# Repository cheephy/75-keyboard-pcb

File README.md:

# 75% keyboard
 A test project following master zen's "How to make a keyboard from scratch" to make a gmmk pro 75% layout style keybord using KiCad and FreeCad.

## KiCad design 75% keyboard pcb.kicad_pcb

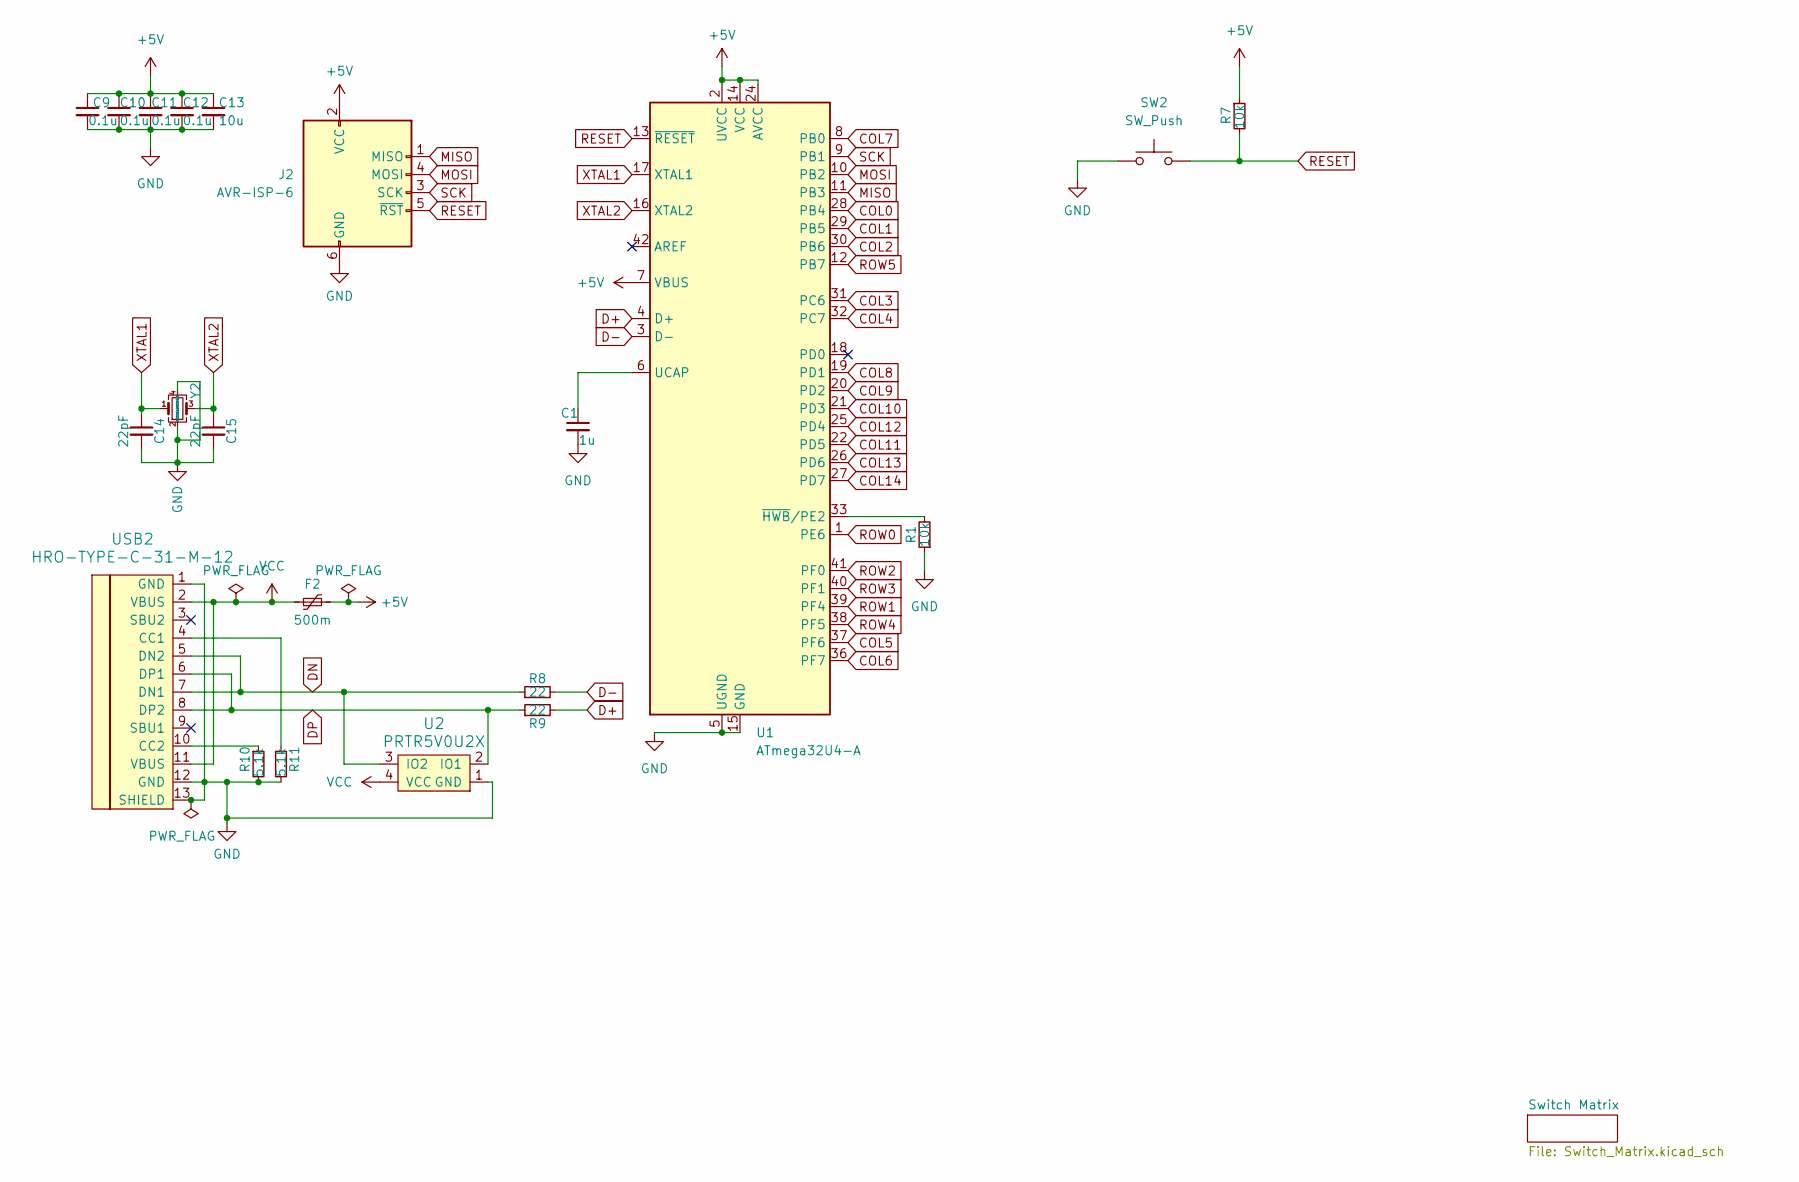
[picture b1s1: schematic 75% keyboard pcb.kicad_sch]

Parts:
C1: 1u; C_0805_2012Metric_Pad1.18x1.45mm_HandSolder
C9, C10, C11, C12: 0.1u; C_0805_2012Metric_Pad1.18x1.45mm_HandSolder
C13: 10u; C_0805_2012Metric_Pad1.18x1.45mm_HandSolder
C14, C15: 22pF; C_0805_2012Metric_Pad1.18x1.45mm_HandSolder
F2: 500m; Fuse_1206_3216Metric_Pad1.42x1.75mm_HandSolder
J2: AVR-ISP-6; Reset_Pretty-Mask
R1, R7: 10k; R_0805_2012Metric_Pad1.20x1.40mm_HandSolder
R8, R9: 22; R_0805_2012Metric_Pad1.20x1.40mm_HandSolder
R10, R11: 5.1k; R_0805_2012Metric_Pad1.20x1.40mm_HandSolder
SW2: SW_Push; SW_SPST_SKQG_WithStem
U1: ATmega32U4-A; TQFP-44_10x10mm_P0.8mm
U2: PRTR5V0U2X; SOT143B
USB2: HRO-TYPE-C-31-M-12; HRO-TYPE-C-31-M-12-HandSoldering
Y2: X322516MOB4SI; Crystal_SMD_3225-4Pin_3.2x2.5mm_HandSoldering

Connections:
+5V: C9.1, C10.1, C11.1, C12.1, C13.1, F2.2, J2.2 (VCC), R7.1, U1.2 (UVCC), U1.7 (VBUS), U1.14 (VCC), U1.24 (AVCC), U1.34 (VCC), U1.44 (AVCC)
COL0: U1.28 (PB4); also elsewhere on the board
COL1: U1.29 (PB5); also elsewhere on the board
COL2: U1.30 (PB6); also elsewhere on the board
COL3: U1.31 (PC6); also elsewhere on the board
COL4: U1.32 (PC7); also elsewhere on the board
COL5: U1.37 (PF6); also elsewhere on the board
COL6: U1.36 (PF7); also elsewhere on the board
COL7: U1.8 (PB0); also elsewhere on the board
COL8: U1.19 (PD1); also elsewhere on the board
COL9: U1.20 (PD2); also elsewhere on the board
COL10: U1.21 (PD3); also elsewhere on the board
COL11: U1.22 (PD5); also elsewhere on the board
COL12: U1.25 (PD4); also elsewhere on the board
COL13: U1.26 (PD6); also elsewhere on the board
COL14: U1.27 (PD7); also elsewhere on the board
D+: R9.2, U1.4 (D+)
D-: R8.2, U1.3 (D-)
DN: R8.1, U2.3 (IO2), USB2.5 (DN2), USB2.7 (DN1)
DP: R9.1, U2.2 (IO1), USB2.6 (DP1), USB2.8 (DP2)
GND: C1.2, C9.2, C10.2, C11.2, C12.2, C13.2, C14.2, C15.2, J2.6 (GND), R1.1, R10.2, R11.2, SW2.1, U1.5 (UGND), U1.15 (GND), U1.23 (GND), U1.35 (GND), U1.43 (GND), U2.1 (GND), USB2.1 (GND), USB2.12 (GND), USB2.13 (SHIELD), Y2.2, Y2.4
MISO: J2.1 (MISO), U1.11 (PB3)
MOSI: J2.4 (MOSI), U1.10 (PB2)
unnamed: C1.1, U1.6 (UCAP)
unnamed: R1.2, U1.33 (~HWB/PE2)
unnamed: R11.1, USB2.4 (CC1)
unnamed: R10.1, USB2.10 (CC2)
RESET: J2.5 (~RST), R7.2, SW2.2, U1.13 (~RESET)
ROW0: U1.1 (PE6); also elsewhere on the board
ROW2: U1.41 (PF0); also elsewhere on the board
ROW3: U1.40 (PF1); also elsewhere on the board
ROW5: U1.12 (PB7); also elsewhere on the board
SCK: J2.3 (SCK), U1.9 (PB1)
VCC: F2.1, U2.4 (VCC), USB2.2 (VBUS), USB2.11 (VBUS)
XTAL1: C14.1, U1.17 (XTAL1), Y2.1
XTAL2: C15.1, U1.16 (XTAL2), Y2.3

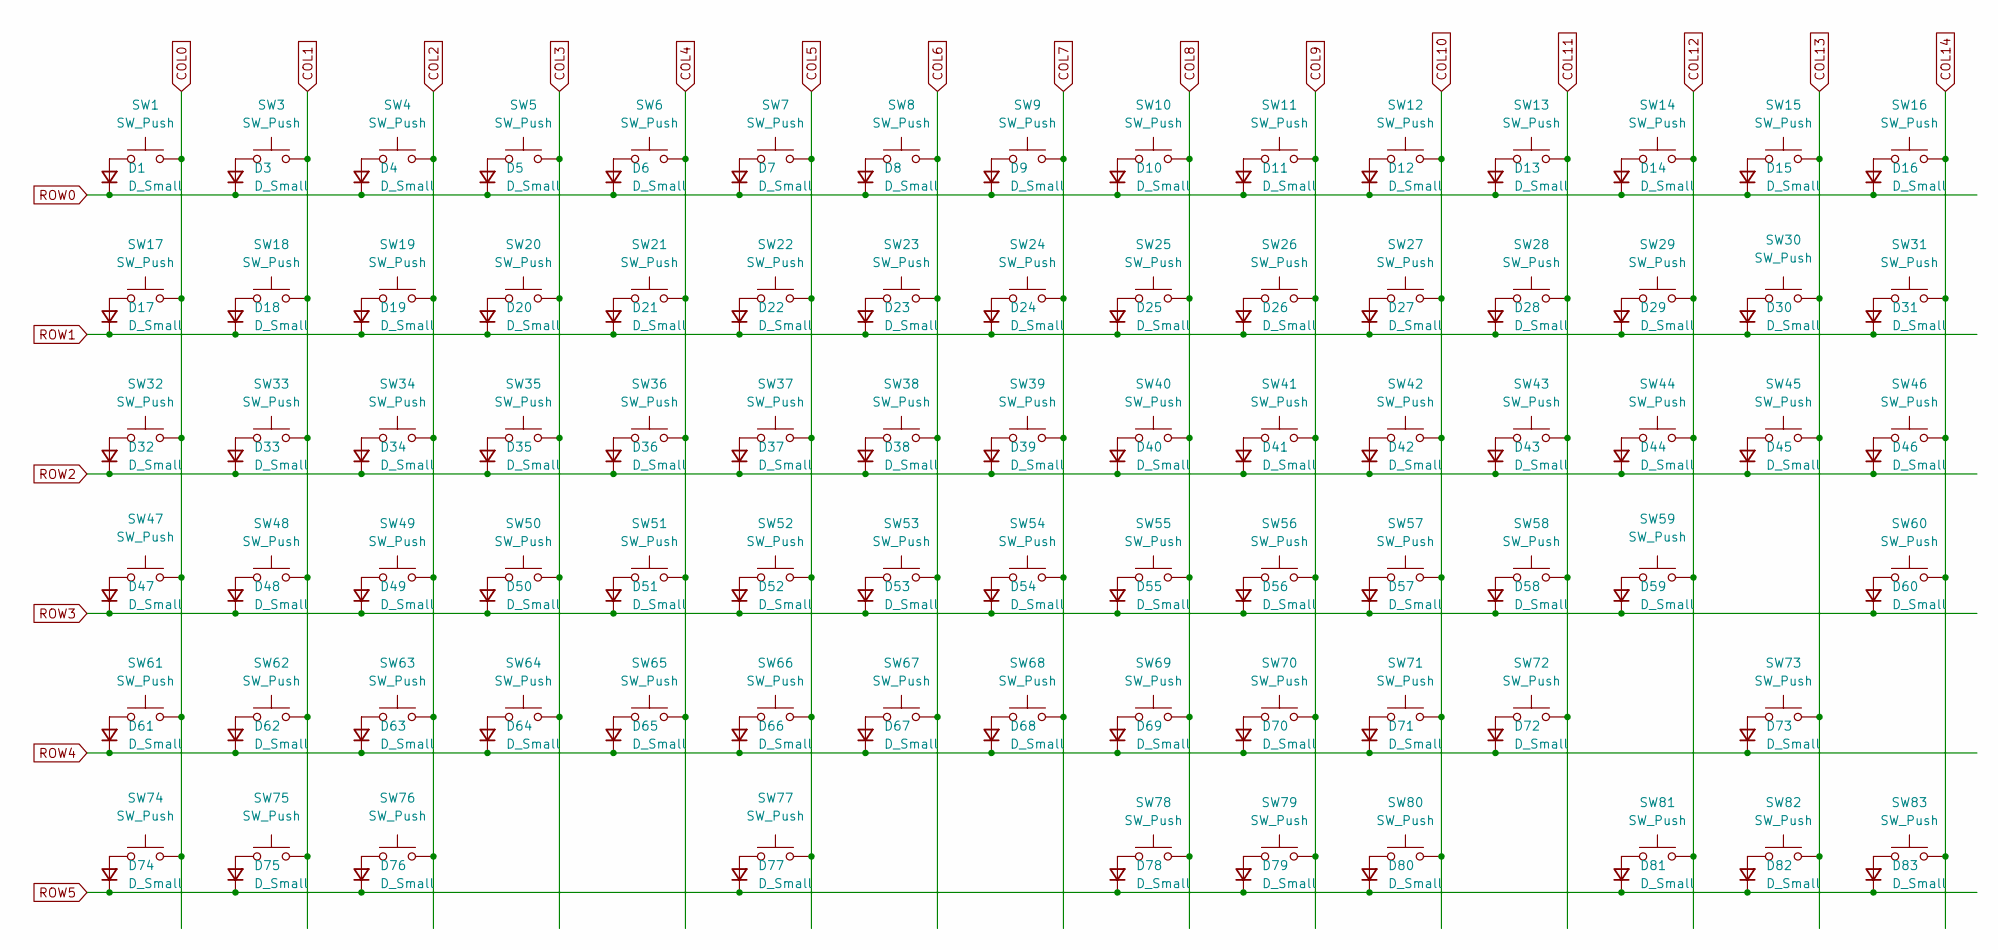
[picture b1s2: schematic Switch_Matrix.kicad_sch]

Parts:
D1, D3, D4, D5, D6, D7, D8, D9, D10, D11, D12, D13, D14, D15, D16, D17, D18, D19, D20, D21, D22, D23, D24, D25, D26, D27, D28, D29, D30, D31, D32, D33, D34, D35, D36, D37, D38, D39, D40, D41, D42, D43, D44, D45, D46, D47, D48, D49, D50, D51, D52, D53, D54, D55, D56, D57, D58, D59, D60, D61, D62, D63, D64, D65, D66, D67, D68, D69, D70, D71, D72, D73, D74, D75, D76, D77, D78, D79, D80, D81, D82, D83: D_Small; D_SOD-123
SW1, SW3, SW4, SW5, SW6, SW7, SW8, SW9, SW10, SW11, SW12, SW13, SW14, SW15, SW16, SW17, SW18, SW19, SW20, SW21, SW22, SW23, SW24, SW25, SW26, SW27, SW28, SW29, SW31, SW33, SW34, SW35, SW36, SW37, SW38, SW39, SW40, SW41, SW42, SW43, SW44, SW46, SW48, SW49, SW50, SW51, SW52, SW53, SW54, SW55, SW56, SW57, SW58, SW60, SW62, SW63, SW64, SW65, SW66, SW67, SW68, SW69, SW70, SW71, SW73, SW78, SW79, SW80, SW81, SW82, SW83: SW_Push; SW_Hotswap_Kailh_MX_Plated_1.00u
SW30: SW_Push; SW_Hotswap_Kailh_MX_Plated_2.00u
SW32, SW45: SW_Push; SW_Hotswap_Kailh_MX_Plated_1.50u
SW47, SW72: SW_Push; SW_Hotswap_Kailh_MX_Plated_1.75u
SW59, SW61: SW_Push; SW_Hotswap_Kailh_MX_Plated_2.25u
SW74, SW75, SW76: SW_Push; SW_Hotswap_Kailh_MX_Plated_1.25u
SW77: SW_Push; SW_Hotswap_Kailh_MX_Plated_6.25u

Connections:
COL0: SW1.2, SW17.2, SW32.2, SW47.2, SW61.2, SW74.2; also elsewhere on the board
COL1: SW3.2, SW18.2, SW33.2, SW48.2, SW62.2, SW75.2; also elsewhere on the board
COL2: SW4.2, SW19.2, SW34.2, SW49.2, SW63.2, SW76.2; also elsewhere on the board
COL3: SW5.2, SW20.2, SW35.2, SW50.2, SW64.2; also elsewhere on the board
COL4: SW6.2, SW21.2, SW36.2, SW51.2, SW65.2; also elsewhere on the board
COL5: SW7.2, SW22.2, SW37.2, SW52.2, SW66.2, SW77.2; also elsewhere on the board
COL6: SW8.2, SW23.2, SW38.2, SW53.2, SW67.2; also elsewhere on the board
COL7: SW9.2, SW24.2, SW39.2, SW54.2, SW68.2; also elsewhere on the board
COL8: SW10.2, SW25.2, SW40.2, SW55.2, SW69.2, SW78.2; also elsewhere on the board
COL9: SW11.2, SW26.2, SW41.2, SW56.2, SW70.2, SW79.2; also elsewhere on the board
COL10: SW12.2, SW27.2, SW42.2, SW57.2, SW71.2, SW80.2; also elsewhere on the board
COL11: SW13.2, SW28.2, SW43.2, SW58.2, SW72.2; also elsewhere on the board
COL12: SW14.2, SW29.2, SW44.2, SW59.2, SW81.2; also elsewhere on the board
COL13: SW15.2, SW30.2, SW45.2, SW73.2, SW82.2; also elsewhere on the board
COL14: SW16.2, SW31.2, SW46.2, SW60.2, SW83.2; also elsewhere on the board
unnamed: D1.2 (A), SW1.1
unnamed: D3.2 (A), SW3.1
unnamed: D4.2 (A), SW4.1
unnamed: D5.2 (A), SW5.1
unnamed: D6.2 (A), SW6.1
unnamed: D7.2 (A), SW7.1
unnamed: D8.2 (A), SW8.1
unnamed: D9.2 (A), SW9.1
unnamed: D10.2 (A), SW10.1
unnamed: D11.2 (A), SW11.1
unnamed: D12.2 (A), SW12.1
unnamed: D13.2 (A), SW13.1
unnamed: D14.2 (A), SW14.1
unnamed: D15.2 (A), SW15.1
unnamed: D16.2 (A), SW16.1
unnamed: D17.2 (A), SW17.1
unnamed: D18.2 (A), SW18.1
unnamed: D19.2 (A), SW19.1
unnamed: D20.2 (A), SW20.1
unnamed: D21.2 (A), SW21.1
unnamed: D22.2 (A), SW22.1
unnamed: D23.2 (A), SW23.1
unnamed: D24.2 (A), SW24.1
unnamed: D25.2 (A), SW25.1
unnamed: D26.2 (A), SW26.1
unnamed: D27.2 (A), SW27.1
unnamed: D28.2 (A), SW28.1
unnamed: D29.2 (A), SW29.1
unnamed: D30.2 (A), SW30.1
unnamed: D31.2 (A), SW31.1
unnamed: D32.2 (A), SW32.1
unnamed: D33.2 (A), SW33.1
unnamed: D34.2 (A), SW34.1
unnamed: D35.2 (A), SW35.1
unnamed: D36.2 (A), SW36.1
unnamed: D37.2 (A), SW37.1
unnamed: D38.2 (A), SW38.1
unnamed: D39.2 (A), SW39.1
unnamed: D40.2 (A), SW40.1
unnamed: D41.2 (A), SW41.1
unnamed: D42.2 (A), SW42.1
unnamed: D43.2 (A), SW43.1
unnamed: D44.2 (A), SW44.1
unnamed: D45.2 (A), SW45.1
unnamed: D46.2 (A), SW46.1
unnamed: D47.2 (A), SW47.1
unnamed: D48.2 (A), SW48.1
unnamed: D49.2 (A), SW49.1
unnamed: D50.2 (A), SW50.1
unnamed: D51.2 (A), SW51.1
unnamed: D52.2 (A), SW52.1
unnamed: D53.2 (A), SW53.1
unnamed: D54.2 (A), SW54.1
unnamed: D55.2 (A), SW55.1
unnamed: D56.2 (A), SW56.1
unnamed: D57.2 (A), SW57.1
unnamed: D58.2 (A), SW58.1
unnamed: D59.2 (A), SW59.1
unnamed: D60.2 (A), SW60.1
unnamed: D61.2 (A), SW61.1
unnamed: D62.2 (A), SW62.1
unnamed: D63.2 (A), SW63.1
unnamed: D64.2 (A), SW64.1
unnamed: D65.2 (A), SW65.1
unnamed: D66.2 (A), SW66.1
unnamed: D67.2 (A), SW67.1
unnamed: D68.2 (A), SW68.1
unnamed: D69.2 (A), SW69.1
unnamed: D70.2 (A), SW70.1
unnamed: D71.2 (A), SW71.1
unnamed: D72.2 (A), SW72.1
unnamed: D73.2 (A), SW73.1
unnamed: D74.2 (A), SW74.1
unnamed: D75.2 (A), SW75.1
unnamed: D76.2 (A), SW76.1
unnamed: D77.2 (A), SW77.1
unnamed: D78.2 (A), SW78.1
unnamed: D79.2 (A), SW79.1
unnamed: D80.2 (A), SW80.1
unnamed: D81.2 (A), SW81.1
unnamed: D82.2 (A), SW82.1
unnamed: D83.2 (A), SW83.1
ROW0: D1.1 (K), D3.1 (K), D4.1 (K), D5.1 (K), D6.1 (K), D7.1 (K), D8.1 (K), D9.1 (K), D10.1 (K), D11.1 (K), D12.1 (K), D13.1 (K), D14.1 (K), D15.1 (K), D16.1 (K); also elsewhere on the board
ROW2: D32.1 (K), D33.1 (K), D34.1 (K), D35.1 (K), D36.1 (K), D37.1 (K), D38.1 (K), D39.1 (K), D40.1 (K), D41.1 (K), D42.1 (K), D43.1 (K), D44.1 (K), D45.1 (K), D46.1 (K); also elsewhere on the board
ROW3: D47.1 (K), D48.1 (K), D49.1 (K), D50.1 (K), D51.1 (K), D52.1 (K), D53.1 (K), D54.1 (K), D55.1 (K), D56.1 (K), D57.1 (K), D58.1 (K), D59.1 (K), D60.1 (K); also elsewhere on the board
ROW5: D74.1 (K), D75.1 (K), D76.1 (K), D77.1 (K), D78.1 (K), D79.1 (K), D80.1 (K), D81.1 (K), D82.1 (K), D83.1 (K); also elsewhere on the board

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
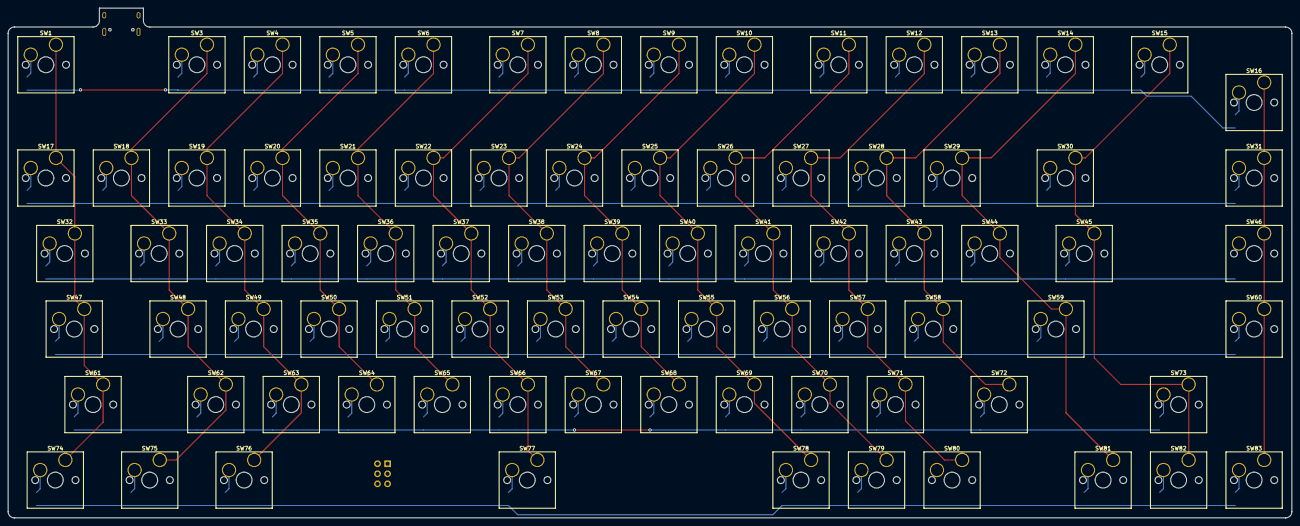
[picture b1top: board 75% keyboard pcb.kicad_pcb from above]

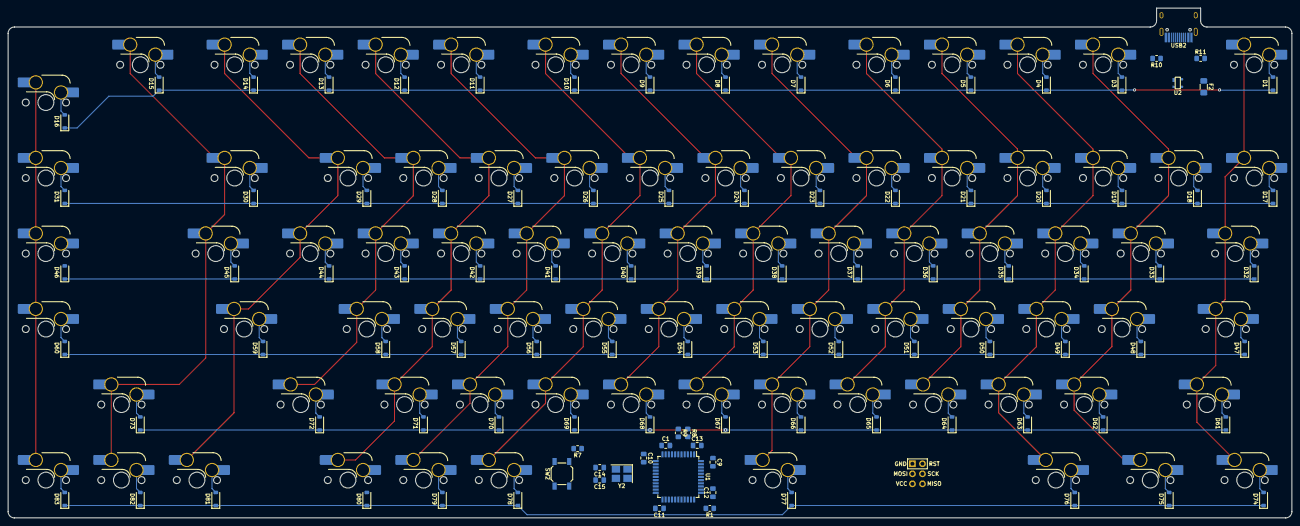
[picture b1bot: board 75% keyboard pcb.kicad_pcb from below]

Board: 2 copper layers, 323.9 x 128.6 mm, 185 parts (103 on the bottom side), 120 nets.

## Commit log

2024-07-24 File Update
    Added in all the libraries needed for the project so I can continue it on my other pc.
